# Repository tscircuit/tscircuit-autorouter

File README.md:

# @tscircuit/capacity-autorouter

An MIT-licensed PCB autorouter made for usage with [tscircuit](https://github.com/tscircuit/tscircuit). This is the builtin autorouter.

The autorouter is composed of hundreds of algorithms organized in a Pipeline. The autorouter uses successive approximation and [Hypergraphs](https://blog.autorouting.com/p/hypergraph-autorouting) rather than sequential routing.

[View Online Playground](https://autorouter.tscircuit.com) &middot; [tscircuit docs](https://docs.tscircuit.com) &middot; [discord](https://tscircuit.com/join) &middot; [twitter](https://x.com/seveibar) &middot; [try tscircuit online](https://tscircuit.com) &middot; [Report/Debug Autorouter Bugs](https://docs.tscircuit.com/contributing/report-autorouter-bugs)

Want to understand how the autorouter works? Read this [blog post](https://blog.autorouting.com/p/hypergraph-autorouting)

## How to file a bug report

1. You should have [created a bug report via the tscircuit errors tab](https://docs.tscircuit.com/contributing/report-autorouter-bugs)
2. Run `bun run bug-report <bug-report-url>` to download the report and create a debugging fixture file in the `examples/bug-reports` directory, you can then find the bug report in the server (via `bun run start`)
3. Or run `bun run bug-report-with-test <bug-report-url>` to download the report, create the fixture, and scaffold a matching snapshot test under `tests/bugs`

Or [run the Create Bug Report workflow](https://github.com/tscircuit/capacity-autorouter/actions/workflows/create-bug-report.yml) to automatically create a PR with the bug report (maintainers only)

## Installation

```bash
bun add @tscircuit/capacity-autorouter
```

## Usage as a Library

### Basic Usage

```typescript
import { AutoroutingPipelineSolver } from "@tscircuit/capacity-autorouter"

// Create a solver with SimpleRouteJson input
const solver = new AutoroutingPipelineSolver(simpleRouteJson)

// Run the solver until completion
while (!solver.solved && !solver.failed) {
  solver.step()
}

// Check if solving was successful
if (solver.failed) {
  console.error("Routing failed:", solver.error)
} else {
  // Get the routing results as SimpleRouteJson with traces
  const resultWithRoutes = solver.getOutputSimpleRouteJson()

  // Use the resulting routes in your application
  console.log(
    `Successfully routed ${resultWithRoutes.traces?.length} connections`
  )
}
```

### Simplifying Existing Traces

Use `AutoroutingPipelineSolver11_Simplification` when the input already
contains routed traces and only needs post-route cleanup. This pipeline does
not route missing SRJ connections. Constant-width traces are simplified while
variable-width traces retain their exact copper widths and geometry.

```typescript
import { AutoroutingPipelineSolver11_Simplification } from "@tscircuit/capacity-autorouter"

const solver = new AutoroutingPipelineSolver11_Simplification(simpleRouteJson)
solver.solve()

if (solver.failed) {
  throw new Error(solver.error ?? "Trace simplification failed")
}

const simplified = solver.getOutputSimpleRouteJson()
```

### Input Format: SimpleRouteJson

Pipeline 9 supports `minTraceToHoleEdgeClearance` (mm) with `isHole`
obstacles, independently of pad clearance.

The input to the autorouter is a `SimpleRouteJson` object with the following structure:

```typescript
interface SimpleRouteJson {
  layerCount: number
  minTraceWidth: number
  obstacles: Obstacle[]
  connections: Array<SimpleRouteConnection>
  buses?: Array<SimpleRouteBus>
  allowViaInPad?: boolean
  bounds: { minX: number; maxX: number; minY: number; maxY: number }
  traces?: SimplifiedPcbTraces // Optional for input
}

interface Obstacle {
  type: "rect"
  layers: string[]
  center: { x: number; y: number }
  width: number
  height: number
  ccwRotationDegrees?: number
  connectedTo: string[] // TraceIds
  isCopperPour?: boolean
  offBoardConnectsTo?: string[] // TraceIds connected off-board
}

interface SimpleRouteConnection {
  name: string
  pointsToConnect: Array<SingleLayerConnectionPoint | MultiLayerConnectionPoint>
}

type SingleLayerConnectionPoint = {
  x: number
  y: number
  layer: string
  layers?: never
}

type MultiLayerConnectionPoint = {
  x: number
  y: number
  layers: string[]
  layer?: never
}

interface SimpleRouteBus {
  busId: string
  connectionNames: string[] // Ordered SimpleRouteConnection names
  maxLengthSkew?: number // Maximum routed-length difference in millimeters
  traceWidth?: number // Resolved copper width in millimeters
  allowedLayers?: string[] // Legal routing layers, including terminal layers
}

interface DifferentialPair {
  connectionNames: [string, string]
  lengthTolerance: number // Maximum pair skew in millimeters
  traceGap?: number // Resolved edge-to-edge copper gap in millimeters
  maxUncoupledLength?: number // Maximum uncoupled length in millimeters
}
```

Pipelines 4–9 validate connection points in the first preprocessing stage.
On-board points must be inside `bounds`, including its edges. An outside point
stops routing with `solved = false`, `failed = true`, and an `error` identifying
the connection, point, coordinates, and bounds. Connections marked `isOffBoard`
are exempt.

Connection points use exactly one representation: `layer` for a fixed routing
layer, or `layers` for a terminal accessible on multiple routing layers. Never
include both fields. The optional `never` properties enforce this distinction
in TypeScript; they are not JSON fields to emit. For multilayer points, the first
entry is the primary layer. Obstacle and via `layers` arrays describe their
physical copper span and are separate from the connection-point representation.

`maxLengthSkew` records the maximum permitted routed-length difference for the
bus. Bus metadata is preserved in the output so routing implementations can
apply the constraint without losing the original membership or ordering.
`traceWidth`, `traceGap`, and `allowedLayers` are resolved routing geometry;
stackup-aware impedance targets should be converted to these dimensions before
creating SimpleRouteJson.

Via-in-pad repair is disabled by default because it generally requires filled
and capped vias. Set `allowViaInPad: true` only when the fabrication process
supports it.

### Output Format

The `getOutputSimpleRouteJson()` method returns the original `SimpleRouteJson` with a populated `traces` property. The traces are represented as `SimplifiedPcbTraces`:

```typescript
type SimplifiedPcbTraces = Array<{
  type: "pcb_trace"
  pcb_trace_id: string // TraceId
  route: Array<
    | {
        route_type: "wire"
        x: number
        y: number
        width: number
        layer: string
      }
    | {
        route_type: "via"
        x: number
        y: number
        to_layer: string
        from_layer: string
      }
  >
}>
```

### Advanced Configuration

You can provide optional configuration parameters to the solver:

```typescript
const solver = new CapacityMeshSolver(simpleRouteJson, {
  // Optional: Manually set capacity planning depth (otherwise automatically calculated)
  capacityDepth: 7,

  // Optional: Set the target minimum capacity for automatic depth calculation
  // Lower values result in finer subdivisions (higher depth)
  targetMinCapacity: 0.5,
})
```

By default, the solver will automatically calculate the optimal `capacityDepth` to achieve a target minimum capacity of 0.5 based on the board dimensions. This automatic calculation ensures that the smallest subdivision cells have an appropriate capacity for routing.

### Visualization Support

For debugging or interactive applications, you can use the `visualize()` method to get a visualization of the current routing state:

```typescript
// Get visualization data that can be rendered with graphics-debug
const visualization = solver.visualize()
```

## Development

To work on this library:

```bash
# Install dependencies
bun install

# Start the interactive development environment
bun run start

# Run tests
bun test

# Build the library
bun run build
```

## Maintainer resources

Track routing performance and benchmark results in the [Autorouter Benchmark Dashboard](https://autorouter-benchmark-dashboard.vercel.app/).

### DRC failure dataset (SRJ33)

[dataset-srj33-drc-failures](https://github.com/tscircuit/dataset-srj33-drc-failures)
contains 37 distinct inputs with at least one measured Pipeline 9 relaxed DRC
issue. The [original benchmark](https://github.com/tscircuit/tscircuit-autorouter/actions/runs/33978041068)
retained 12 samples and excluded 19 DRC passes. An
[additional audit](https://github.com/tscircuit/tscircuit-autorouter/actions/runs/33980539076)
added 25 bug-report inputs that completed routing with DRC issues after the
recent DRC fix. Original IDs remain 001–006, 010–013, 020, and 025; additions use
032–056.

```sh
bun scripts/run-sample.ts --pipeline 9 --dataset srj33 --sample 1
```

Use `srj33` in the benchmark workflow's dataset input, or open
`benchmarks/dataset-srj33` in Cosmos. CLI `--sample` selects by position:
`--sample 12` loads `sample025`, and `--sample 37` loads `sample056`.
Cosmos uses the sample IDs. The dataset records source links, pinned revisions,
and Pipeline 9 selection evidence. Saved outputs for the original 12 are their
historical Pipeline 7 baseline; additions include Pipeline 9 outputs and exact
DRC errors.

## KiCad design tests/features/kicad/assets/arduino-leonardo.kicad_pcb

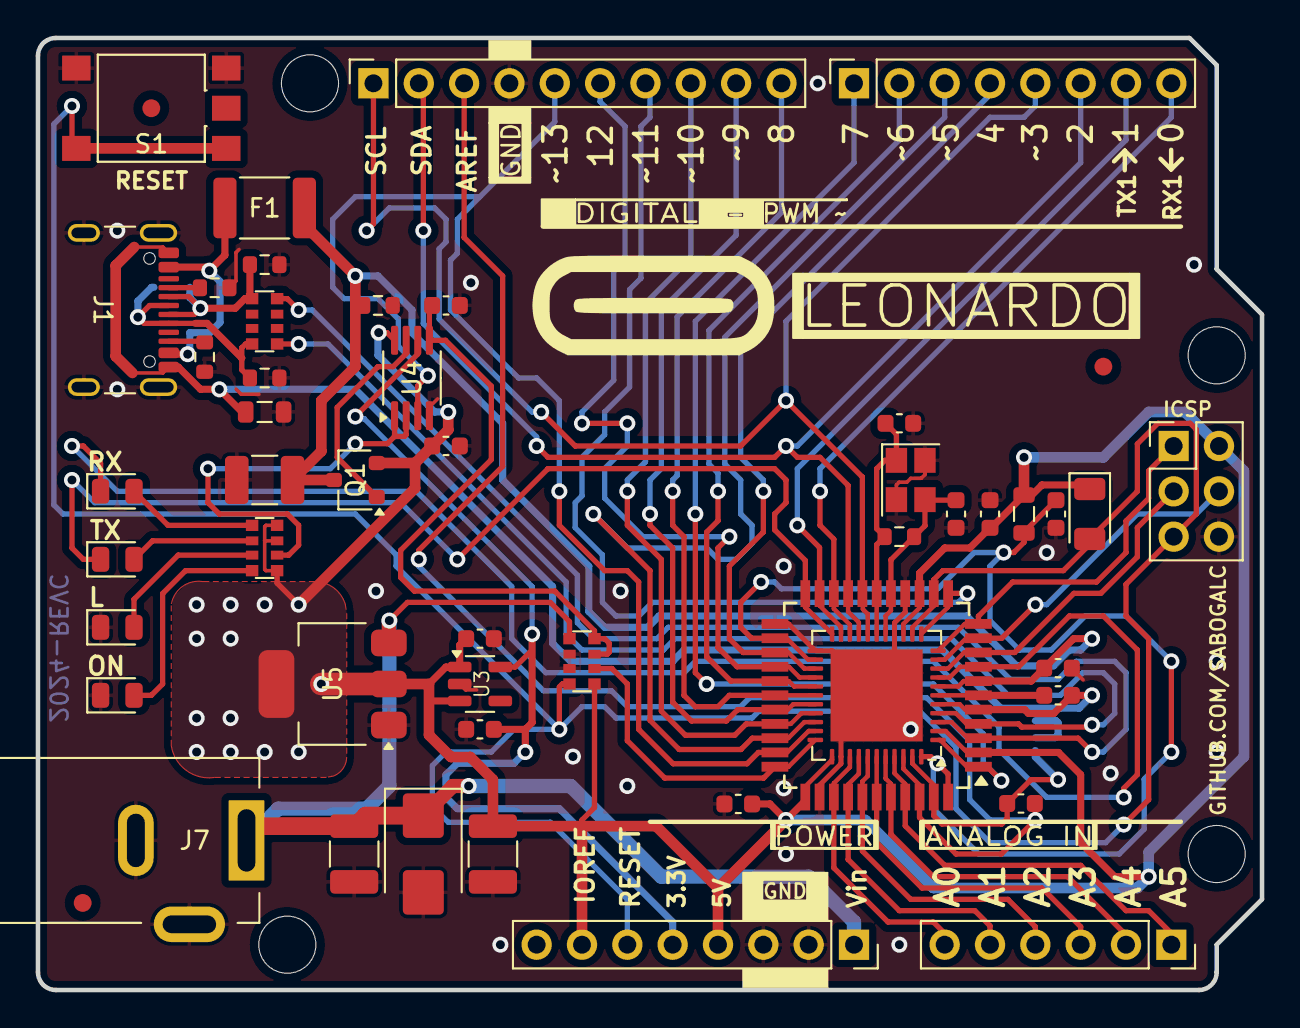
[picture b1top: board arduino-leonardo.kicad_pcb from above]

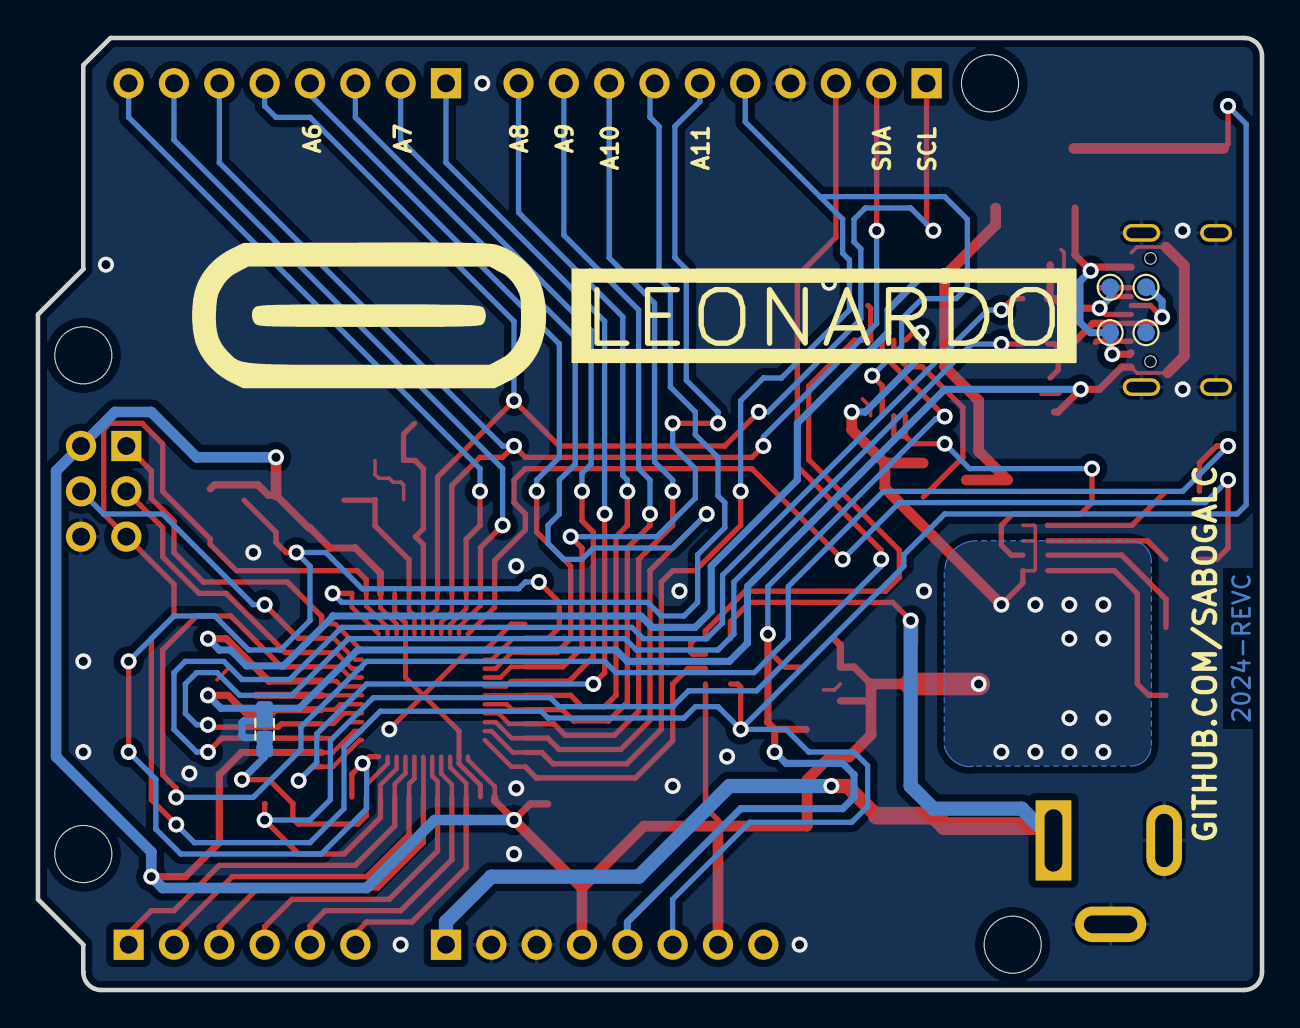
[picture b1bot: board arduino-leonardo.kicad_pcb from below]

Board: 2 copper layers, 68.6 x 53.3 mm, 57 parts (6 on the bottom side), 53 nets.

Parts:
C1, C2, C6, C9, C13, C22: 100n; C_0603_1608Metric
C3, C4: 22p; C_0603_1608Metric
C5, C7, C11, C14: 1u; C_0603_1608Metric
C8, C10, C12: 10u; C_1210_3225Metric_Pad1.33x2.70mm_HandSolder
D1: M7; D_SMB
D2: CD1206-S01575; D_1206_3216Metric
D3, D5, D6: YELLOW; LED_0805_2012Metric
D4: GREEN; LED_0805_2012Metric
F1: MF-MSMF050-2; Fuse_1812_4532Metric_Pad1.30x3.40mm_HandSolder
FB1, FB2: 1kΩ@100MHz; L_0805_2012Metric
FID1, FID2, FID3: Fiducial; Fiducial_1mm_Mask2mm
J1: USB_C_Receptacle_USB2.0_16P; USB_C_Receptacle_GCT_USB4105-xx-A_16P_TopMnt_Horizontal
J2: PPTC101LFBN-RC; PinSocket_1x10_P2.54mm_Vertical
J3, J4: PPTC081LFBN-RC; PinSocket_1x08_P2.54mm_Vertical
J5: PPTC061LFBN-RC; PinSocket_1x06_P2.54mm_Vertical
J6: M20-9980345; PinHeader_2x03_P2.54mm_Vertical
J7: PJ-102AH; BarrelJack_Kycon_KLDX-0202-xC_Horizontal
Q1: FDN340P; SC-59
R1: 1M; R_0603_1608Metric
R2, R3: NM; R_0603_1608Metric
R4: 10k; R_0603_1608Metric
R5, R6: 5k1; R_0603_1608Metric
RN1: 10k; R_Array_Convex_4x0612
RN2: 1k; R_Array_Convex_4x0612
RN3: 22R; R_Array_Convex_4x0612
S1: TS06-667-30-BK-100-G-SMT-TR; SW_TS06-667-30-BK-100-G-SMT-TR
TP1, TP2, TP3, TP4: TestPoint; TestPoint_Pad_D1.0mm
U1: ATMEGA32U4-XU; QFN-44-1EP_7x7mm_P0.5mm_EP5.15x5.15mm
U2: ATMEGA32U4-XU; TQFP-44_10x10mm_P0.8mm
U3: LP2985-3.3; SOT-23-5
U4: LMV358IDGKR; MSOP-8_3x3mm_P0.65mm
U5: NCP1117-5.0_SOT223; SOT-223-3_TabPin2
Y1: ECS-160-18-33-JGN-TR; Crystal_SMD_SeikoEpson_FA238-4Pin_3.2x2.5mm
Z1, Z2: 5pF@1MHz; R_0603_1608Metric

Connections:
+3.3V: C14.2, J4.5, U3.5 (VOUT), U4.6
+5V: C1.1, C2.1, C11.2, C12.1, C13.1, D2.1 (K), FB1.1, J4.4, J4.7, J6.2, Q1.2 (S), RN1.5 (R4.2), RN2.1 (R1.1), RN2.3 (R3.1), RN2.4 (R4.1), U1.2 (UVCC), U1.14 (VCC), U1.34 (VCC1), U2.2 (UVCC), U2.14 (VCC), U2.34 (VCC1), U3.1 (VIN), U3.3 (ON/~OFF), U4.8 (VCC+), U5.2 (VO)
A0: J5.6, U1.36 ((ADC7/TDI)PF7), U2.36 ((ADC7/TDI)PF7)
A1: J5.5, U1.37 ((ADC6/TDO)PF6), U2.37 ((ADC6/TDO)PF6)
A2: J5.4, U1.38 ((ADC5/TMS)PF5), U2.38 ((ADC5/TMS)PF5)
A3: J5.3, U1.39 ((ADC4/TCK)PF4), U2.39 ((ADC4/TCK)PF4)
A4: J5.2, U1.40 ((ADC1)PF1), U2.40 ((ADC1)PF1)
A5: J5.1, U1.41 ((ADC0)PF0), U2.41 ((ADC0)PF0)
AGND: C6.1, R2.1, U1.43 (GND3), U2.43 (GND3)
AREF: C6.2, J2.3, U1.42 (AREF), U2.42 (AREF)
AVCC: C5.1, FB1.2, U1.24 (AVCC), U1.44 (AVCC1), U2.24 (AVCC), U2.44 (AVCC1)
CC1: J1.A5 (CC1), R5.1
CC2: J1.B5 (CC2), R6.1
CMP: C22.2, RN1.7 (R2.2), RN1.8 (R1.2), U4.5
D0/RX: J3.8, U1.20 ((RXD1/AIN1/INT2)PD2), U2.20 ((RXD1/AIN1/INT2)PD2)
D1/TX: J3.7, U1.21 ((TXD1/INT3)PD3), U2.21 ((TXD1/INT3)PD3)
D2/SDA: J2.2, J3.6, U1.19 ((SDA/INT1)PD1), U2.19 ((SDA/INT1)PD1)
D3/SCL: J2.1, J3.5, U1.18 ((OC0B/SCL/INT0)PD0), U2.18 ((OC0B/SCL/INT0)PD0)
D4: J3.4, U1.25 ((ICP1/ADC8)PD4), U2.25 ((ICP1/ADC8)PD4)
D5*: J3.3, U1.31 ((OC3A/#0C4A)PC6), U2.31 ((OC3A/#0C4A)PC6)
D6*: J3.2, U1.27 ((T0/OC4D/ADC10)PD7), U2.27 ((T0/OC4D/ADC10)PD7)
D7: J3.1, U1.1 ((INT6/AIN0)PE6), U2.1 ((INT6/AIN0)PE6)
D+: J1.A6 (D+), J1.B6 (D+), RN3.8 (R1.2), TP3.1, Z1.1
D-: J1.A7 (D-), J1.B7 (D-), RN3.5 (R4.2), TP2.1, Z2.1
GATE_CMD: Q1.1 (G), U4.7
GND: C1.2, C2.2, C3.1, C4.2, C5.2, C8.2, C9.1, C10.2, C11.1, C12.2, C13.2, C14.1, C22.1, D1.2 (A), D3.1 (K), D4.1 (K), FB2.2, J1.S1 (SHIELD), J2.4, J4.2, J4.3, J6.6, J7.2, J7.3, R2.2, R3.1, R4.1, R5.2, R6.2, RN1.2 (R2.1), RN1.3 (R3.1), S1.3, S1.4, TP4.1, U1.15 (GND), U1.23 (GND1), U1.35 (GND2), U1.45 (PAD), U2.15 (GND), U2.23 (GND1), U2.35 (GND2), U3.2 (GND), U4.4 (GND), U5.1 (GND), Y1.2, Y1.4, Z1.2, Z2.2
HWB: RN1.6 (R3.2), U1.33 ((#HWB)PE2), U2.33 ((#HWB)PE2)
IO8: J2.10, U1.28 ((ADC11/PCINT4)PB4), U2.28 ((ADC11/PCINT4)PB4)
IO9*: J2.9, U1.29 ((PCINT5/OC1A/#OC4B/ADC12)PB5), U2.29 ((PCINT5/OC1A/#OC4B/ADC12)PB5)
IO10*: J2.8, U1.30 ((PCINT6/OC1B/OC4B/ADC13)PB6), U2.30 ((PCINT6/OC1B/OC4B/ADC13)PB6)
IO11*: J2.7, U1.12 ((PCINT7/OC0A/OC1C/#RTS)PB7), U2.12 ((PCINT7/OC0A/OC1C/#RTS)PB7)
IO12: J2.6, U1.26 ((T1/#OC4D/ADC9)PD6), U2.26 ((T1/#OC4D/ADC9)PD6)
IO13*: J2.5, U1.32 ((ICP3/CLK0/OC4A)PC7), U2.32 ((ICP3/CLK0/OC4A)PC7), U4.3
LL: RN2.2 (R2.1), U4.1, U4.2
MISO: J6.1, U1.11 ((PD0/MISO/PCINT3)PB3), U2.11 ((PD0/MISO/PCINT3)PB3)
MOSI: J6.4, U1.10 ((PDI/MOSI/PCINT2)PB2), U2.10 ((PDI/MOSI/PCINT2)PB2)
unnamed: D3.2 (A), RN2.7 (R2.2)
unnamed: D4.2 (A), RN2.8 (R1.2)
unnamed: D5.2 (A), RN2.6 (R3.2)
unnamed: D6.2 (A), RN2.5 (R4.2)
RD+: RN3.1 (R1.1), U1.4 (D+), U2.4 (D+)
RD-: RN3.4 (R4.1), U1.3 (D-), U2.3 (D-)
RESET: D2.2 (A), J4.6, J6.5, RN1.4 (R4.1), S1.1, S1.2, U1.13 (RESET), U2.13 (RESET)
RXLED: D6.1 (K), U1.8 ((SS/PCINT0)PB0), U2.8 ((SS/PCINT0)PB0)
SCK: J6.3, U1.9 ((SCLK/PCINT1)PB1), U2.9 ((SCLK/PCINT1)PB1)
TXLED: D5.1 (K), U1.22 ((XCK1/#CTS)PD5), U2.22 ((XCK1/#CTS)PD5)
UCAP: C7.1, U1.6 (UCAP), U2.6 (UCAP)
UGND: C7.2, FB2.1, J1.A1 (GND), J1.A12 (GND), J1.B1 (GND), J1.B12 (GND), R3.2, U1.5 (UGND), U2.5 (UGND)
VBUS: C8.1, C9.2, F1.1, Q1.3 (D), R4.2, U1.7 (VBUS), U2.7 (VBUS)
VCC: C10.1, D1.1 (K), J4.1, J7.1, RN1.1 (R1.1), U5.3 (VI)
XTAL1: C4.1, R1.1, U1.17 (XTAL1), U2.17 (XTAL1), Y1.1
XTAL2: C3.2, R1.2, U1.16 (XTAL2), U2.16 (XTAL2), Y1.3
XUSB: F1.2, J1.A4 (VBUS), J1.A9 (VBUS), J1.B4 (VBUS), J1.B9 (VBUS), TP1.1
